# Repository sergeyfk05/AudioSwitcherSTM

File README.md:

# Description
This project receives 4 or more audio channels to the input and outputs the first active audio channel in order of priority. 
If there is at least one active channel, then the logic unit is supplied to the LED and AMP outputs, thereby including a relay 
for the sound amplifier and an LED. The number of channels, sensitivity settings, pins can be configured in the settings. 
There are also other settings in the maine. All settings are well documented. There are tinctures that allow you to take 
measurements with different frequencies, individual for each channel, and much more.</br></br>

# Harware requirements
Code is written for STM32F103C8T6. Also you can use chinees' analogue.</br></br>

# Circuit and circuit board
You can find circuit, circuit board and gerber-files(needed for to order circuit board) in /Eagle/ directory. You can order the circuit board in <a href="https://JLCPCB.com">JLCPCB.com</a>.
It is very cheap, only $ 2 for 5 pcs.

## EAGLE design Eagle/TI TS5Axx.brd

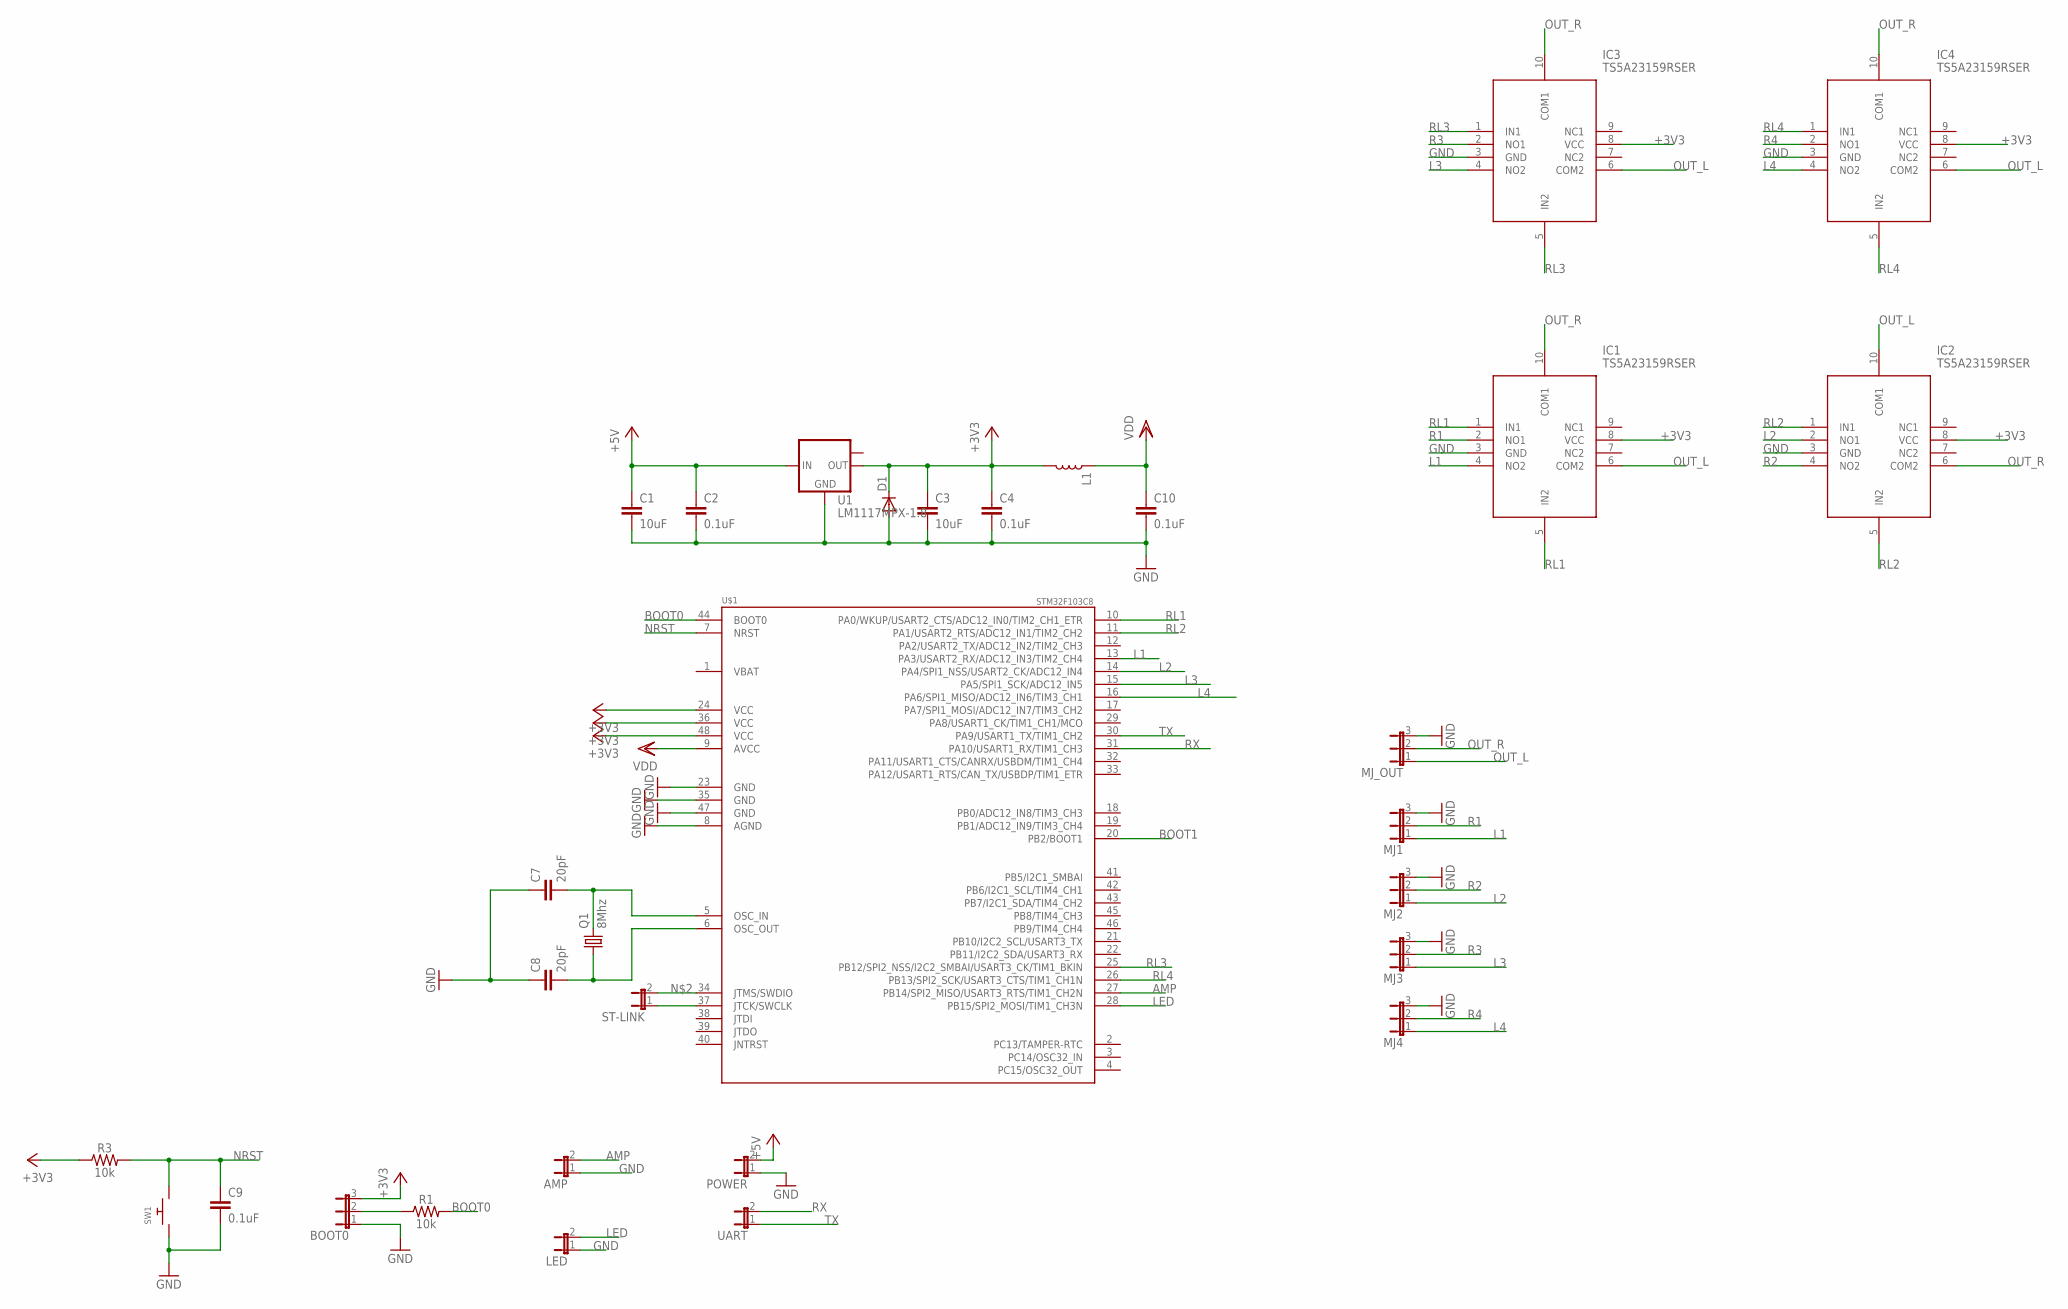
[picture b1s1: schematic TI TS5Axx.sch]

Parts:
AMP: JP1E; JP1
BOOT0: JP2E; JP2
C1, C3: 10uF; 0805
C2, C4, C9, C10: 0.1uF; 0805
C7, C8: 20pF; 0805
D1: DIODE-DO214AA; DO214AA
IC1, IC2, IC3, IC4: TS5A23159RSER; QFN50P150X200X60-10N
L1: INDUCTORFB-30OHM; 0603
LED: JP1E; JP1
MJ1, MJ2, MJ3, MJ4: JP2E; JP2
MJ_OUT: JP2E; JP2
POWER: JP1E; JP1
Q1: 8Mhz; HC49/S
R1, R3: 10k; 0603
ST-LINK: JP1E; JP1
SW1: SWITCH_PUSHBUTTONEVQ-PE; TACT_PANA-EVQ
U1: LM1117MPX-1.8; SOT223
U$1: STM32F103C8; LQFP48-7X7
UART: JP1E; JP1

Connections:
+3V3: BOOT0.3, C3.1, C4.1, D1.C, IC1.8 (VCC), IC2.8 (VCC), IC3.8 (VCC), IC4.8 (VCC), L1.2, R3.1, U1.2 (OUT), U$1.24 (VCC), U$1.36 (VCC), U$1.48 (VCC)
+5V: C1.1, C2.1, POWER.2, U1.3 (IN)
AMP: AMP.2, U$1.27 (PB14/SPI2_MISO/USART3_RTS/TIM1_CH2N)
BOOT0: R1.2, U$1.44 (BOOT0)
BOOT1: U$1.20 (PB2/BOOT1)
GND: AMP.1, BOOT0.1, C1.2, C2.2, C3.2, C4.2, C7.1, C8.1, C9.2, C10.2, D1.A, IC1.3 (GND), IC2.3 (GND), IC3.3 (GND), IC4.3 (GND), LED.1, MJ1.3, MJ2.3, MJ3.3, MJ4.3, MJ_OUT.3, POWER.1, SW1.P$1, U1.1 (GND), U$1.8 (AGND), U$1.23 (GND), U$1.35 (GND), U$1.47 (GND)
L1: IC1.4 (NO2), MJ1.1, U$1.13 (PA3/USART2_RX/ADC12_IN3/TIM2_CH4)
L2: IC2.2 (NO1), MJ2.1, U$1.14 (PA4/SPI1_NSS/USART2_CK/ADC12_IN4)
L3: IC3.4 (NO2), MJ3.1, U$1.15 (PA5/SPI1_SCK/ADC12_IN5)
L4: IC4.4 (NO2), MJ4.1, U$1.16 (PA6/SPI1_MISO/ADC12_IN6/TIM3_CH1)
LED: LED.2, U$1.28 (PB15/SPI2_MOSI/TIM1_CH3N)
unnamed: BOOT0.2, R1.1
unnamed: ST-LINK.2, U$1.34 (JTMS/SWDIO)
unnamed: C8.2, Q1.1, U$1.6 (OSC_OUT)
unnamed: C7.2, Q1.2, U$1.5 (OSC_IN)
unnamed: ST-LINK.1, U$1.37 (JTCK/SWCLK)
NRST: C9.1, R3.2, SW1.P$2, U$1.7 (NRST)
OUT_L: IC1.6 (COM2), IC2.10 (COM1), IC3.6 (COM2), IC4.6 (COM2), MJ_OUT.1
OUT_R: IC1.10 (COM1), IC2.6 (COM2), IC3.10 (COM1), IC4.10 (COM1), MJ_OUT.2
R1: IC1.2 (NO1), MJ1.2
R2: IC2.4 (NO2), MJ2.2
R3: IC3.2 (NO1), MJ3.2
R4: IC4.2 (NO1), MJ4.2
RL1: IC1.1 (IN1), IC1.5 (IN2), U$1.10 (PA0/WKUP/USART2_CTS/ADC12_IN0/TIM2_CH1_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)
RL2: IC2.1 (IN1), IC2.5 (IN2), U$1.11 (PA1/USART2_RTS/ADC12_IN1/TIM2_CH2)
RL3: IC3.1 (IN1), IC3.5 (IN2), U$1.25 (PB12/SPI2_NSS/I2C2_SMBAI/USART3_CK/TIM1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)
RL4: IC4.1 (IN1), IC4.5 (IN2), U$1.26 (PB13/SPI2_SCK/USART3_CTS/TIM1_CH1N)
RX: U$1.31 (PA10/USART1_RX/TIM1_CH3), UART.2
TX: U$1.30 (PA9/USART1_TX/TIM1_CH2), UART.1
VBAT: U$1.1 (VBAT)
VDD: C10.1, L1.1, U$1.9 (AVCC)

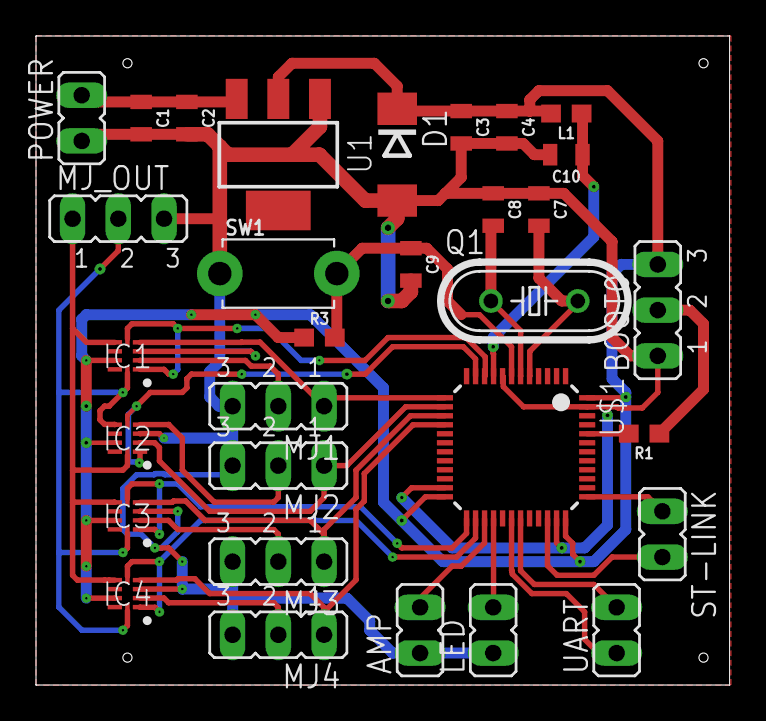
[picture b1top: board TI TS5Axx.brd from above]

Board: 2 copper layers, 38.5 x 36.1 mm, 31 parts (0 on the bottom side), 29 nets.

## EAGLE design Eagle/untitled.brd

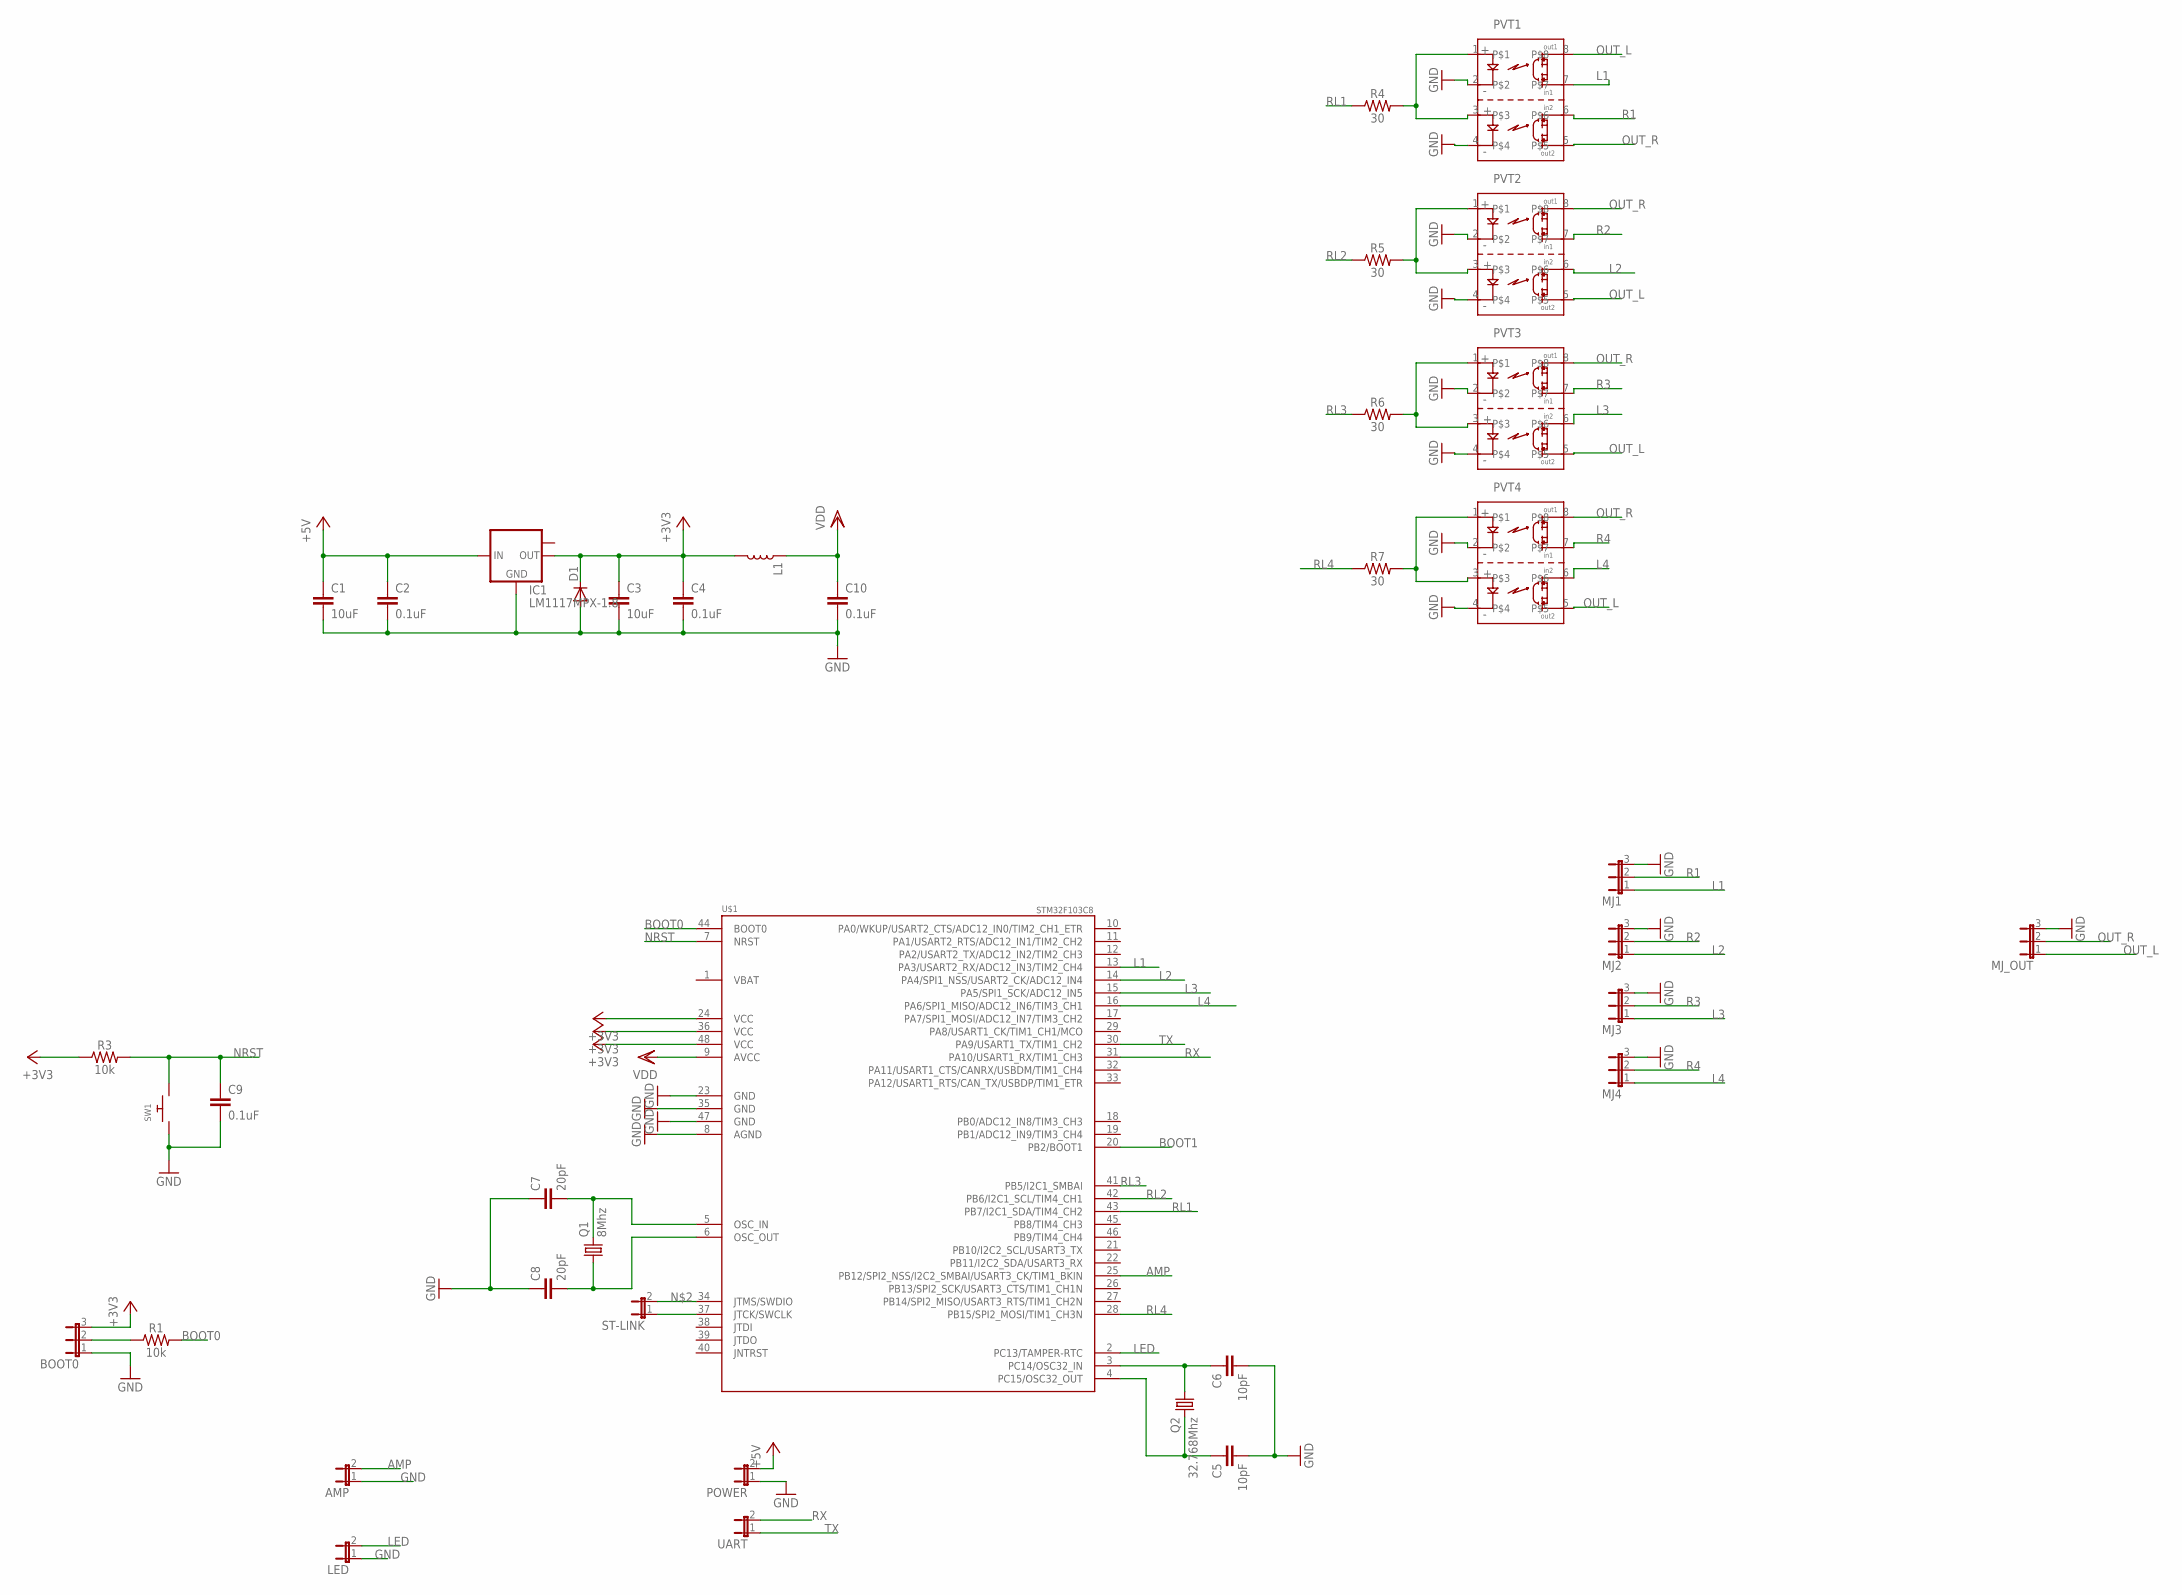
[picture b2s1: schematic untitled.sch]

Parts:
AMP: JP1E; JP1
BOOT0: JP2E; JP2
C1, C3: 10uF; 0805
C2, C4, C9, C10: 0.1uF; 0805
C5, C6: 10pF; 0805
C7, C8: 20pF; 0805
D1: DIODE-DO214AA; DO214AA
IC1: LM1117MPX-1.8; SOT223
L1: INDUCTORFB-30OHM; 0603
LED: JP1E; JP1
MJ1, MJ2, MJ3, MJ4: JP2E; JP2
MJ_OUT: JP2E; JP2
POWER: JP1E; JP1
PVT1, PVT2, PVT3, PVT4: PVT322A; DIP-8
Q1: 8Mhz; HC49/S
Q2: 32.768Mhz; HC49/S
R1, R3: 10k; 0603
R4, R5, R6, R7: 30; 0603
ST-LINK: JP1E; JP1
SW1: SWITCH_PUSHBUTTONEVQ-PE; TACT_PANA-EVQ
U$1: STM32F103C8; LQFP48-7X7
UART: JP1E; JP1

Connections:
+3V3: BOOT0.3, C3.1, C4.1, D1.C, IC1.2 (OUT), L1.2, R3.1, U$1.24 (VCC), U$1.36 (VCC), U$1.48 (VCC)
+5V: C1.1, C2.1, IC1.3 (IN), POWER.2
AMP: AMP.2, U$1.25 (PB12/SPI2_NSS/I2C2_SMBAI/USART3_CK/TIM1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)
BOOT0: R1.2, U$1.44 (BOOT0)
BOOT1: U$1.20 (PB2/BOOT1)
GND: AMP.1, BOOT0.1, C1.2, C2.2, C3.2, C4.2, C5.2, C6.2, C7.1, C8.1, C9.2, C10.2, D1.A, IC1.1 (GND), LED.1, MJ1.3, MJ2.3, MJ3.3, MJ4.3, MJ_OUT.3, POWER.1, PVT1.2, PVT1.4, PVT2.2, PVT2.4, PVT3.2, PVT3.4, PVT4.2, PVT4.4, SW1.P$1, U$1.8 (AGND), U$1.23 (GND), U$1.35 (GND), U$1.47 (GND)
L1: MJ1.1, PVT1.7, U$1.13 (PA3/USART2_RX/ADC12_IN3/TIM2_CH4)
L2: MJ2.1, PVT2.6, U$1.14 (PA4/SPI1_NSS/USART2_CK/ADC12_IN4)
L3: MJ3.1, PVT3.6, U$1.15 (PA5/SPI1_SCK/ADC12_IN5)
L4: MJ4.1, PVT4.6, U$1.16 (PA6/SPI1_MISO/ADC12_IN6/TIM3_CH1)
LED: LED.2, U$1.2 (PC13/TAMPER-RTC)
unnamed: BOOT0.2, R1.1
unnamed: ST-LINK.2, U$1.34 (JTMS/SWDIO)
unnamed: C6.1, Q2.1, U$1.3 (PC14/OSC32_IN)
unnamed: C8.2, Q1.1, U$1.6 (OSC_OUT)
unnamed: C7.2, Q1.2, U$1.5 (OSC_IN)
unnamed: PVT1.1, PVT1.3, R4.2
unnamed: C5.1, Q2.2, U$1.4 (PC15/OSC32_OUT)
unnamed: PVT2.1, PVT2.3, R5.2
unnamed: ST-LINK.1, U$1.37 (JTCK/SWCLK)
unnamed: PVT3.1, PVT3.3, R6.2
unnamed: PVT4.1, PVT4.3, R7.2
NRST: C9.1, R3.2, SW1.P$2, U$1.7 (NRST)
OUT_L: MJ_OUT.1, PVT1.8, PVT2.5, PVT3.5, PVT4.5
OUT_R: MJ_OUT.2, PVT1.5, PVT2.8, PVT3.8, PVT4.8
R1: MJ1.2, PVT1.6
R2: MJ2.2, PVT2.7
R3: MJ3.2, PVT3.7
R4: MJ4.2, PVT4.7
RL1: R4.1, U$1.43 (PB7/I2C1_SDA/TIM4_CH2)
RL2: R5.1, U$1.42 (PB6/I2C1_SCL/TIM4_CH1)
RL3: R6.1, U$1.41 (PB5/I2C1_SMBAI)
RL4: R7.1, U$1.28 (PB15/SPI2_MOSI/TIM1_CH3N)
RX: U$1.31 (PA10/USART1_RX/TIM1_CH3), UART.2
TX: U$1.30 (PA9/USART1_TX/TIM1_CH2), UART.1
VBAT: U$1.1 (VBAT)
VDD: C10.1, L1.1, U$1.9 (AVCC)

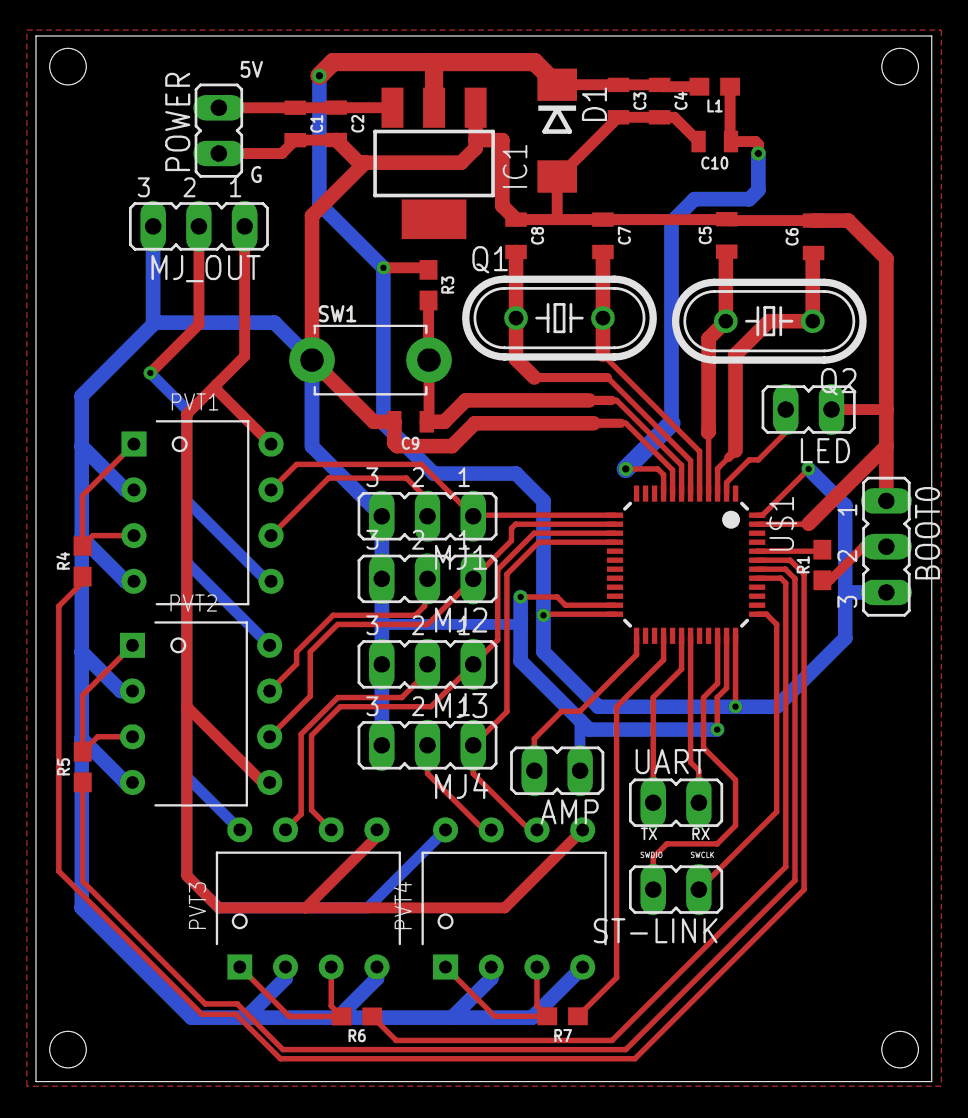
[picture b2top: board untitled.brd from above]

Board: 2 copper layers, 49.8 x 58.1 mm, 38 parts (0 on the bottom side), 35 nets.

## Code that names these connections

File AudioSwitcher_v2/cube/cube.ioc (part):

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Mcu.Name=STM32G030F6Px
Mcu.Package=TSSOP20
Mcu.UserName=STM32G030F6Px
PA0.Mode=IN0
PA0.Signal=ADC1_IN0
PA1.Mode=IN1
PA1.Signal=ADC1_IN1
PA11\ [PA9].GPIOParameters=PinState
PA11\ [PA9].PinState=GPIO_PIN_SET
PA11\ [PA9].Signal=GPIO_Output
PA12\ [PA10].GPIOParameters=PinState
PA12\ [PA10].PinState=GPIO_PIN_SET
PA12\ [PA10].Signal=GPIO_Output
PA2.Mode=IN2
PA2.Signal=ADC1_IN2
PA3.Mode=IN3
PA3.Signal=ADC1_IN3
PA4.Mode=IN4
PA4.Signal=ADC1_IN4
PA5.Mode=IN5
PA5.Signal=ADC1_IN5
PA6.Mode=IN6
PA6.Signal=ADC1_IN6
PA7.Mode=IN7
PA7.Signal=ADC1_IN7
PB0.Signal=GPIO_Output
PB7.Signal=GPIO_Input
PB9.GPIOParameters=PinState
PB9.PinState=GPIO_PIN_SET
PB9.Signal=GPIO_Output
PC15-OSC32_OUT\ (PC15).GPIOParameters=PinState
PC15-OSC32_OUT\ (PC15).PinState=GPIO_PIN_SET
PC15-OSC32_OUT\ (PC15).Signal=GPIO_Output
RCC.HSE_VALUE=8000000
RCC.SYSCLKFreq_VALUE=64000000
RCC.SYSCLKSource=RCC_SYSCLKSOURCE_PLLCLK
board=custom

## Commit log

2019-08-15 Add .gitignore and .gitattributes.
2019-08-15 Add project files.
2019-08-16 one project - one commit)
2019-08-25 final
2019-08-25 add curcuit and readme.md
2019-08-25 edit readme
2019-09-15 added scheme in pdf; added comments in code; changed EAGLE project;
2019-09-15 added circuit board and scheme pictures
2019-09-30 add indicators provider
2019-10-11 add scheme for Texas Instruments' analog switch
2019-12-19 add alternative scheme
2019-12-19 better architecture for channels switching
2019-12-19 fix merge problems
2021-10-17 new schematic
2021-10-18 v2 start
2021-10-18 coded v2
2021-10-19 checkpoint
2021-10-24 good work; testing
2021-10-25 fix schematic
2021-10-26 fix schematic and code
2021-10-27 fix schematic and add ble holder
2021-11-07 add ble board and more slient turn off
2022-01-22 stable fw with IR remote and BLE
2022-01-22 finish 3d

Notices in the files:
parts and their libraries:
SparkFun-Capacitors: Licensing: Creative Commons ShareAlike 4.0 International - https://creativecommons.org/licenses/by-sa/4.0
